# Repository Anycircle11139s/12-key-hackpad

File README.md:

# 16 key hackpad with OLED
This is my 16-key hackpad which has 16 keys and an oled screen. I made it so I can use all 16 keys for different shortcuts and stuff, because I'm not bothered to move  my hand an extra 2mm every 10 hours. This is my CAD, I looked at the kicad pcb and measured with the ruler to find the measurements to place the oled and keys in the correct places. The CADing was pretty easy overall.

This is my PCB design, after creating the schematic, I imported it into the pcb editor and arranged the parts, which was pretty easy. But then I had to do the wiring, I started from the top and went down but it was extremely annoying and mind-numbing, finally, after a while, I managed to complete it. I have so many vias... :( I also had a bit of trouble fitting it into the 100 by 100 millimetre pcb size limit, but I barely made it.

This is my schematic, I started by creating the 4 by 4 matrix for the buttons, then I connected it to the rp2040. Next, I added the oled and connected that to the rp2040. The hardest part was creating the matrix which took me a while and a lot of reddit searching, but after that, it got a lot simpler.

BOM: 16x Cherry MX Switches 1x XIAO RP2040 16x Blank DSA Keycaps 4x M3x16 Bolt 4x M3 Heatset 1x 0.91 Oled display 8x SK6812 Mini RGB LEDs

| Name | Quantity | Cost Per Item (USD) | Total (USD) | Purpose | Distributor | Link |
|------|----------|---------------------|-------------|---------|-------------|------|
| PCB fabrication and shipping | 1 | $3.50 | $3.50 | pcb for my hackpad | JLCPCB | [Link]((https://trade.jlcpcb.com/checkout/payMethod/?unionSettleId=2ab23cae292f4e70994453dde486af05&systemType=order_pcb&orderTypes=order_pcb&calType=PRE_CAL&couponDemo=1)) |
| Ali Express shipping and fees | 1 | $4.73 | $4.73 | Shipping | Ali Express | [Link] |
| M3x5mx4mm heatset inserts | 1 | $4.09 | $4.09 | secure threading for the M3 screw | Ali Express | [Link](https://www.aliexpress.us/item/2255800046543591.html) |
| M3x16mm screws | 1 | $1.05 | $1.05 | Secures top and bottom parts of the cases together | Ali Express | [Link](https://www.aliexpress.us/item/3256805692722422.html?spm=a2g0o.productlist.main.15.6bdaXiwWXiwW4C&utparam-url=scene%3Asearch%7Cquery_from%3Apc_back_same_best%7Cx_object_id%3A1005005879037174%7C_p_origin_prod%3A&algo_pvid=056d9f9f-cd17-4a96-b4b5-7e28a3cb7079&algo_exp_id=056d9f9f-cd17-4a96-b4b5-7e28a3cb7079&pdp_ext_f=%7B%22order%22%3A%2239378%22%2C%22fromPage%22%3A%22search%22%7D&pdp_npi=6%40dis%21USD%211.11%210.99%21%21%211.11%210.99%21%402101f11417740613553598176ea51c%2112000034679037238%21sea%21US%217455183214%21ABX%211%210%21n_tag%3A-29910%3Bd%3A4adcddb6%3Bm03_new_user%3A-29895%3BpisId%3A5000000197847491&gatewayAdapt=4itemAdapt) |
| 1u Key caps | 1 | $3.79 | $3.79 | The covering for the keys | Ali Express | [Link](https://www.aliexpress.com/item/1005008678389468.html?spm=a2g0o.productlist.main.6.5e71STAXSTAXa6&algo_pvid=f8f6b19f-95d8-4d9a-bf05-5c7b79d7c726&algo_exp_id=f8f6b19f-95d8-4d9a-bf05-5c7b79d7c726-5&pdp_ext_f=%7B%22order%22%3A%22158%22%2C%22spu_best_type%22%3A%22price%22%2C%22eval%22%3A%221%22%2C%22fromPage%22%3A%22search%22%7D&pdp_npi=6%40dis%21USD%214.23%212.23%21%21%214.23%212.23%21%40210311c217741745460307955e969e%2112000046204757643%21sea%21AU%217402515296%21X%211%210%21n_tag%3A-29911%3Bd%3Aef1e07f3%3Bm03_new_user%3A-29895%3BpisId%3A5000000202132944&curPageLogUid=USF9TxF5Xjpt&utparam-url=scene%3Asearch%7Cquery_from%3A%7Cx_object_id%3A1005008678389468%7C_p_origin_prod%3A) |
| 5-pin PCB-mount switch | 30 pack (No 20 or 16 option) | $8.00 | $8.00 | The keyboard keys | Ali Express | [Link](https://www.aliexpress.us/item/3256806239135691.html?spm=a2g0o.productlist.main.1.555cY61VY61Voz&algo_pvid=f4678bb1-d8bc-4f13-acc6-d405ddda900a&algo_exp_id=f4678bb1-d8bc-4f13-acc6-d405ddda900a-0&pdp_ext_f=%7B%22order%22%3A%222257%22%2C%22spu_best_type%22%3A%22price%22%2C%22eval%22%3A%221%22%2C%22fromPage%22%3A%22search%22%7D&pdp_npi=6%40dis%21USD%212.96%210.99%21%21%2120.28%216.79%21%40210319b017740604574907332ebb44%2112000037120671469%21sea%21US%217455183214%21ABX%211%210%21n_tag%3A-29910%3Bd%3A4adcddb6%3Bm03_new_user%3A-29895%3BpisId%3A5000000197847458&curPageLogUid=wFaqavLZ7pag&utparam-url=scene%3Asearch%7Cquery_from%3A%7Cx_object_id%3A1005006425450443%7C_p_origin_prod%3A) |
| 5V SK6812MINI-E rgb leds | 10 | $0.283 | $2.83 | Shows colours to indicate signals | Ali Express | [Link](https://www.aliexpress.us/item/3256805154503907.html?spm=a2g0o.cart.0.0.255738daUjnIZC&mp=1&pdp_npi=6%40dis%21USD%21USD%203.88%21USD%202.83%21%21USD%202.83%21%21%21%40210328d417740598605087437e76d7%2112000032670306832%21ct%21US%217455183214%21%211%210%21&_gl=1*ctc1p2*_gcl_aw*R0NMLjE3NzQwNTk2MzMuQ2owS0NRanc0UFBOQmhEOEFSSXNBTW8taWN6aTRJXzhFRUkxVTdYOW5nZHUwR3F6SnFwb29VemlmOGJaQUV5dkF0b2ZXS0tSU0NqTUFya2FBbVZsRUFMd193Y0I.*_gcl_dc*R0NMLjE3NzQwNTk2MzMuQ2owS0NRanc0UFBOQmhEOEFSSXNBTW8taWN6aTRJXzhFRUkxVTdYOW5nZHUwR3F6SnFwb29VemlmOGJaQUV5dkF0b2ZXS0tSU0NqTUFya2FBbVZsRUFMd193Y0I.*_gcl_au*MTM5MDY2MTQ1Ny4xNzc0MDIzODky*_ga*Njc2OTI3NDYwMTEwMDc2LjE3NzQwMjM4ODg0ODQ.*_ga_VED1YSGNC7*czE3NzQwNTc2MzgkbzQkZzEkdDE3NzQwNTk4NjIkajUyJGwwJGgw&gatewayAdapt=glo2usa) |
| 0.91 inch SSD1306 I2C 128x32 OLED display | 1 | $2.85 | $2.85 | Displays information and animations | Ali Express | [Link](https://www.aliexpress.com/item/1005006823025817.html?mp=1&pdp_npi=6@dis!USD!USD%203.03!USD%202.85!!USD%202.85!!!@2101f70717741760867295397e5ca9!12000038417220460!ct!AU!7402515296!!1!0!) |
| Seed Xiao - RP2040 | 1 | $4.68 | $4.68 | Microcontroller - the power source and control | Ali Express | [Link](https://www.aliexpress.com/item/1005008652799938.html?spm=a2g0o.productlist.main.1.6d1dSic1Sic1iz&algo_pvid=2ce7fa80-8a21-431b-8aab-7c89d5b1e36c&algo_exp_id=2ce7fa80-8a21-431b-8aab-7c89d5b1e36c-0&pdp_ext_f=%7B%22order%22%3A%22219%22%2C%22spu_best_type%22%3A%22price%22%2C%22eval%22%3A%221%22%2C%22fromPage%22%3A%22search%22%7D&pdp_npi=6%40dis%21USD%2114.45%214.04%21%21%2199.00%2127.72%21%402103274e17741757575204045eb231%2112000046106276655%21sea%21AU%217402515296%21X%211%210%21n_tag%3A-29911%3Bd%3Aef1e07f3%3Bm03_new_user%3A-29895&curPageLogUid=1OKs76xZs5r6&utparam-url=scene%3Asearch%7Cquery_from%3A%7Cx_object_id%3A1005008652799938%7C_p_origin_prod%3A) |
| Diodes | 1 | $2.74 | $2.74 | Diodes, so no ghost| Ali Express | [Link](https://www.aliexpress.com/item/1005007606166130.html?spm=a2g0o.productlist.main.3.5b632LkK2LkK7y&algo_pvid=5ecd24f1-13f3-4414-b47c-b5f0489edd12&algo_exp_id=5ecd24f1-13f3-4414-b47c-b5f0489edd12-2&pdp_ext_f=%7B%22order%22%3A%2243%22%2C%22eval%22%3A%221%22%2C%22fromPage%22%3A%22search%22%7D&pdp_npi=6%40dis%21USD%212.74%212.63%21%21%2118.80%2118.05%21%402101e2b417741774821175327e5d1b%2112000045210201538%21sea%21AU%217402515296%21X%211%210%21n_tag%3A-29911%3Bd%3Aef1e07f3%3Bm03_new_user%3A-29895%3BpisId%3A5000000202470703&curPageLogUid=ELi0JhSGGJBV&utparam-url=scene%3Asearch%7Cquery_from%3A%7Cx_object_id%3A1005007606166130%7C_p_origin_prod%3A) |
| Case shipping and printing | 1 | $6.50 | $6.50 | Case for hackpad | Printing legion | [Link] |

**Total cost: $38.26**

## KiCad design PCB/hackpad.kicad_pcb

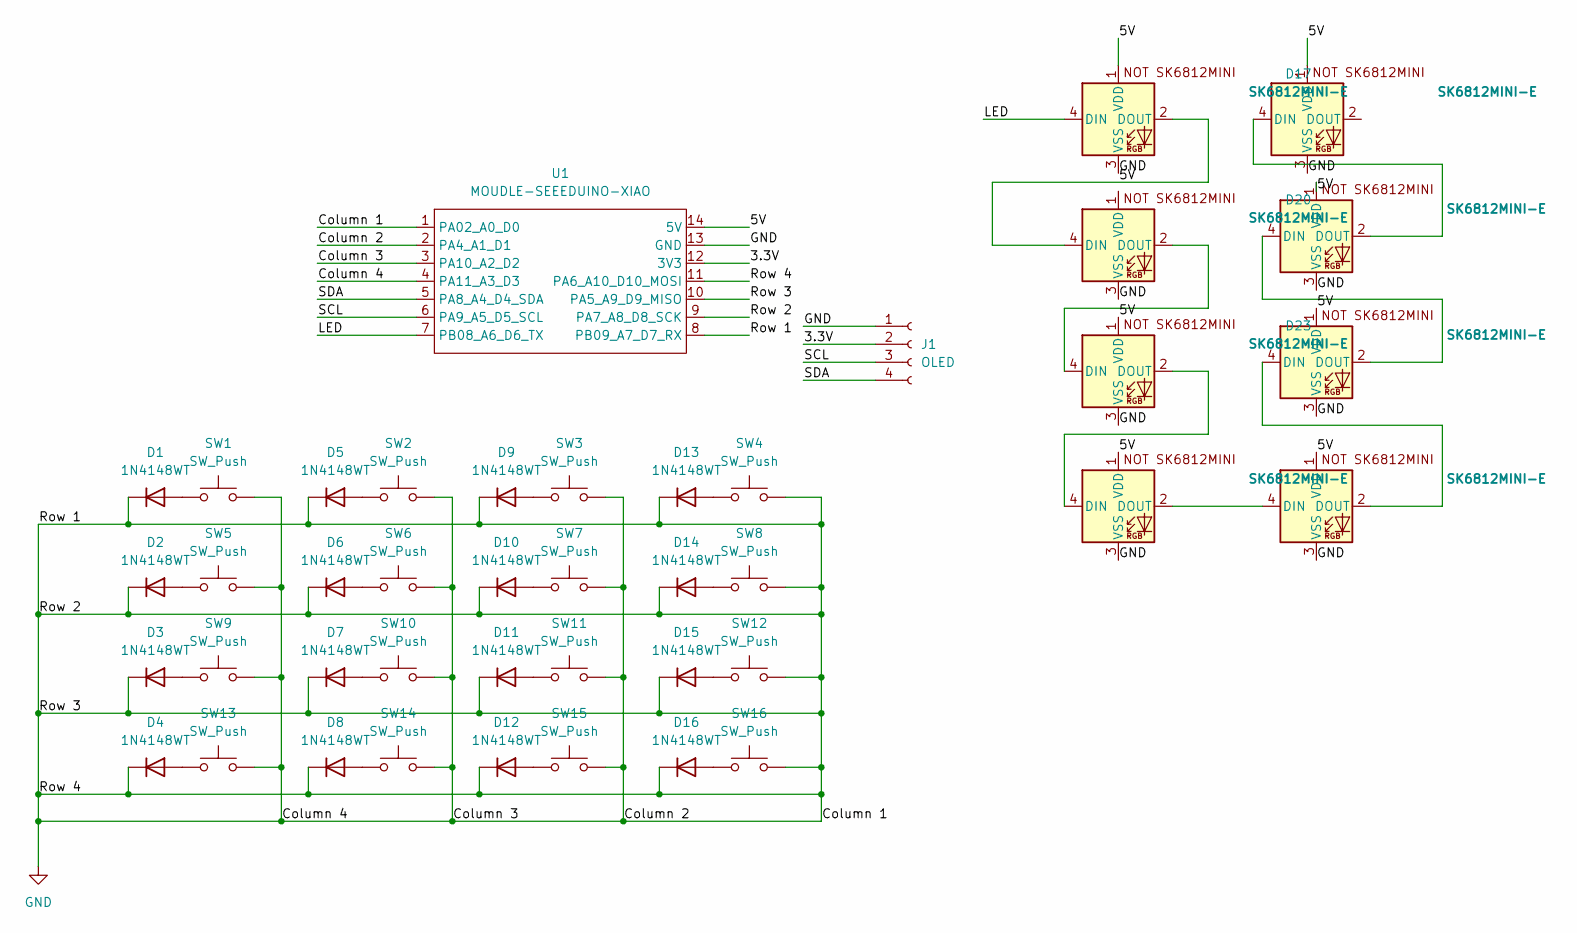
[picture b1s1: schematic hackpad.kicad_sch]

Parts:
D1, D2, D3, D4, D5, D6, D7, D8, D9, D10, D11, D12, D13, D14, D15, D16: 1N4148WT; D_SOD-523
D17, D18, D19, D20, D21, D22, D23, D24: SK6812MINI-E; SK6812MINI-E_fixed
J1: OLED; SSD1306-0.91-OLED-4pin-128x32
SW1, SW2, SW3, SW4, SW5, SW6, SW7, SW8, SW9, SW10, SW11, SW12, SW13, SW14, SW15, SW16: SW_Push; SW_Cherry_MX_1.00u_PCB
U1: MOUDLE-SEEEDUINO-XIAO; XIAO-Generic-Hybrid-14P-2.54-21X17.8MM

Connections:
/3.3V: J1.2, U1.12 (3V3)
/5V: D17.1 (VDD), D17.2 (DOUT), D18.1 (VDD), D19.1 (VDD), D20.4 (DIN), D21.1 (VDD), D22.1 (VDD), D23.1 (VDD), D24.1 (VDD), U1.14 (5V)
/LED: D17.4 (DIN), U1.7 (PB08_A6_D6_TX)
/SCL: J1.3, U1.6 (PA9_A5_D5_SCL)
/SDA: J1.4, U1.5 (PA8_A4_D4_SDA)
GND: D1.1 (K), D2.1 (K), D3.1 (K), D4.1 (K), D5.1 (K), D6.1 (K), D7.1 (K), D8.1 (K), D9.1 (K), D10.1 (K), D11.1 (K), D12.1 (K), D13.1 (K), D14.1 (K), D15.1 (K), D16.1 (K), D17.3 (VSS), D18.3 (VSS), D19.3 (VSS), D20.3 (VSS), D21.3 (VSS), D22.3 (VSS), D23.3 (VSS), D24.3 (VSS), J1.1, SW1.2, SW2.2, SW3.2, SW4.2, SW5.2, SW6.2, SW7.2, SW8.2, SW9.2, SW10.2, SW11.2, SW12.2, SW13.2, SW14.2, SW15.2, SW16.2, U1.1 (PA02_A0_D0), U1.2 (PA4_A1_D1), U1.3 (PA10_A2_D2), U1.4 (PA11_A3_D3), U1.8 (PB09_A7_D7_RX), U1.9 (PA7_A8_D8_SCK), U1.10 (PA5_A9_D9_MISO), U1.11 (PA6_A10_D10_MOSI), U1.13 (GND)
unnamed: D1.2 (A), SW1.1
unnamed: D2.2 (A), SW5.1
unnamed: D3.2 (A), SW9.1
unnamed: D4.2 (A), SW13.1
unnamed: D5.2 (A), SW2.1
unnamed: D6.2 (A), SW6.1
unnamed: D7.2 (A), SW10.1
unnamed: D8.2 (A), SW14.1
unnamed: D9.2 (A), SW3.1
unnamed: D10.2 (A), SW7.1
unnamed: D11.2 (A), SW11.1
unnamed: D12.2 (A), SW15.1
unnamed: D13.2 (A), SW4.1
unnamed: D14.2 (A), SW8.1
unnamed: D15.2 (A), SW12.1
unnamed: D16.2 (A), SW16.1
unnamed: D18.4 (DIN), D23.2 (DOUT)
unnamed: D18.2 (DOUT), D22.4 (DIN)
unnamed: D19.4 (DIN), D21.2 (DOUT)
unnamed: D20.2 (DOUT), D23.4 (DIN)
unnamed: D21.4 (DIN), D24.2 (DOUT)
unnamed: D22.2 (DOUT), D24.4 (DIN)

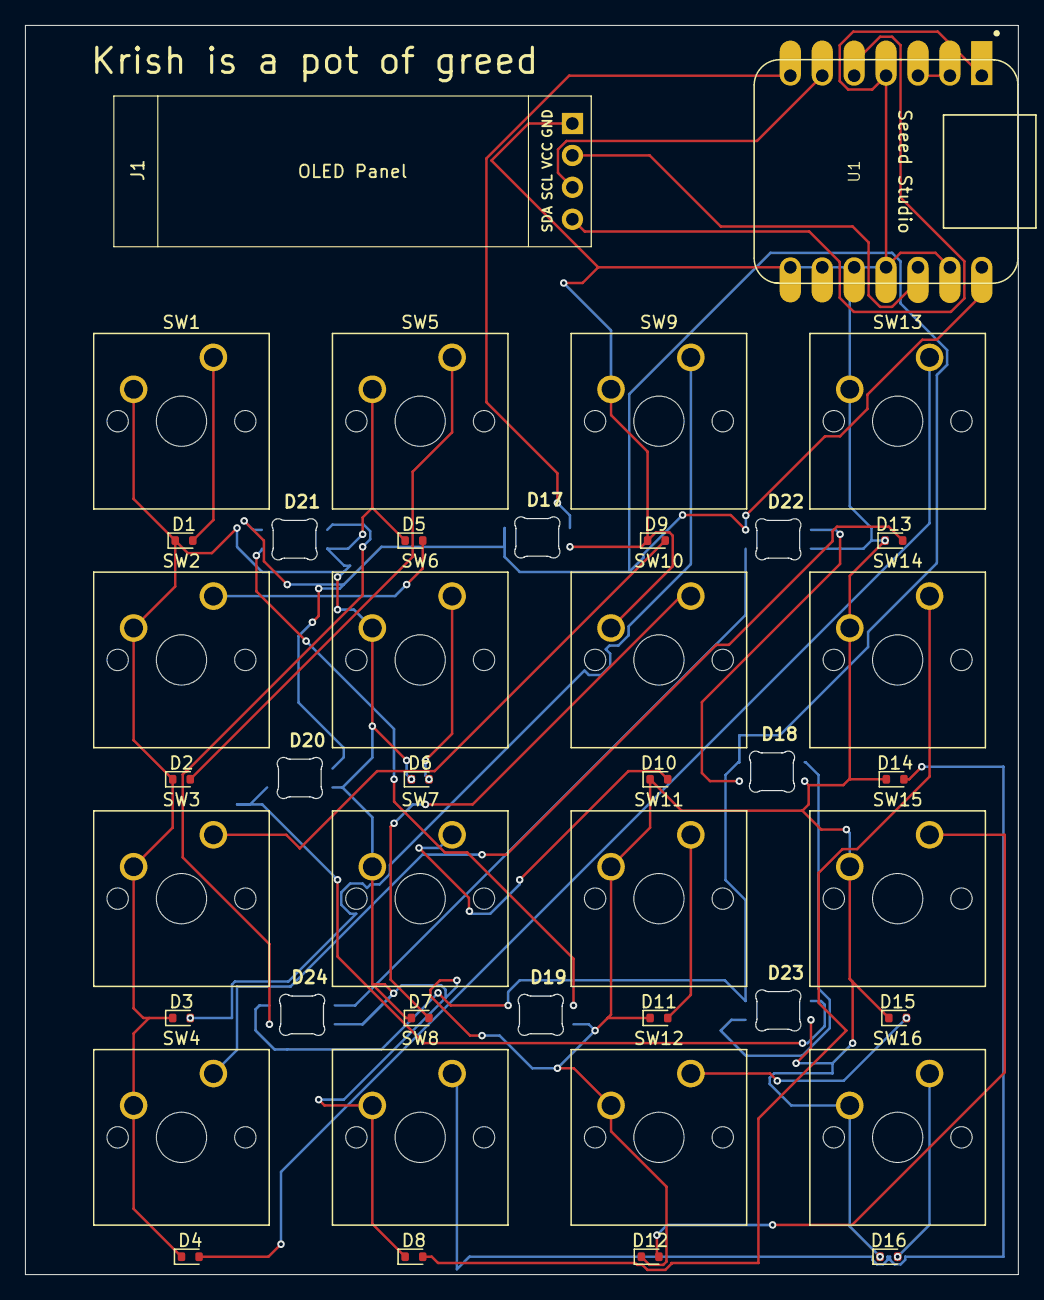
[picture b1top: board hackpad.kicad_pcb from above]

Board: 2 copper layers, 79.0 x 99.4 mm, 42 parts (0 on the bottom side), 28 nets.

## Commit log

2026-03-22 Enhance README with images
    Added images to the README for better visualization.
2026-03-22 Rename Krish hackpad.kicad_sch to Firmware/hackpad.kicad_sch
2026-03-22 Rename Krish hackpad.kicad_pcb to Firmware/hackpad.kicad_pcb
2026-03-22 Rename Krish hackpad.kicad_prl to Firmware/hackpad.kicad_prl
2026-03-22 Rename Krish hackpad.kicad_pro to Firmware/hackpad.kicad_pro
2026-03-22 Fix image tag in README.md
2026-03-22 Rename Final assemby 12 key hackpad.f3z to CAD/Final assemby 12 key hackpad.f3z
2026-03-22 Rename Final assemby 12 key hackpad.step to CAD/Final assemby 12 key hackpad.step
2026-03-22 Rename hackpad.kicad_pcb to hackpad.kicad_pcb
2026-03-22 Rename hackpad.kicad_prl to hackpad.kicad_prl
2026-03-22 Rename hackpad.kicad_pro to hackpad.kicad_pro
2026-03-22 Rename hackpad.kicad_sch to hackpad.kicad_sch
2026-03-22 Initialize keyboard firmware with OLED support
2026-03-22 Initialize keyboard setup with OLED display
2026-03-22 Rename Krish hackpad.kicad_pcb to hackpad.kicad_pcb
2026-03-22 Rename Krish hackpad.kicad_sch to hackpad.kicad_sch
2026-03-22 Rename Krish hackpad.kicad_pro to hackpad.kicad_pro
2026-03-22 Rename Krish hackpad.kicad_prl to hackpad.kicad_prl
2026-03-22 Modify BOM.CSV with updated product links
    Updated entries for PCB fabrication and Ali Express shipping with new links.
2026-03-22 Update BOM.CSV with new items and links
    Updated BOM.CSV to add new items and links, and modify existing entries.
2026-03-22 Update BOM.CSV with new components and links
    Removed items from BOM.CSV and added new entries.
2026-03-22 Update BOM.CSV with new component entries
2026-03-22 Update BOM.CSV with total cost calculation
2026-03-25 Update cost for case printing and shipping
2026-03-28 Refactor comments for hardware and OLED setup
